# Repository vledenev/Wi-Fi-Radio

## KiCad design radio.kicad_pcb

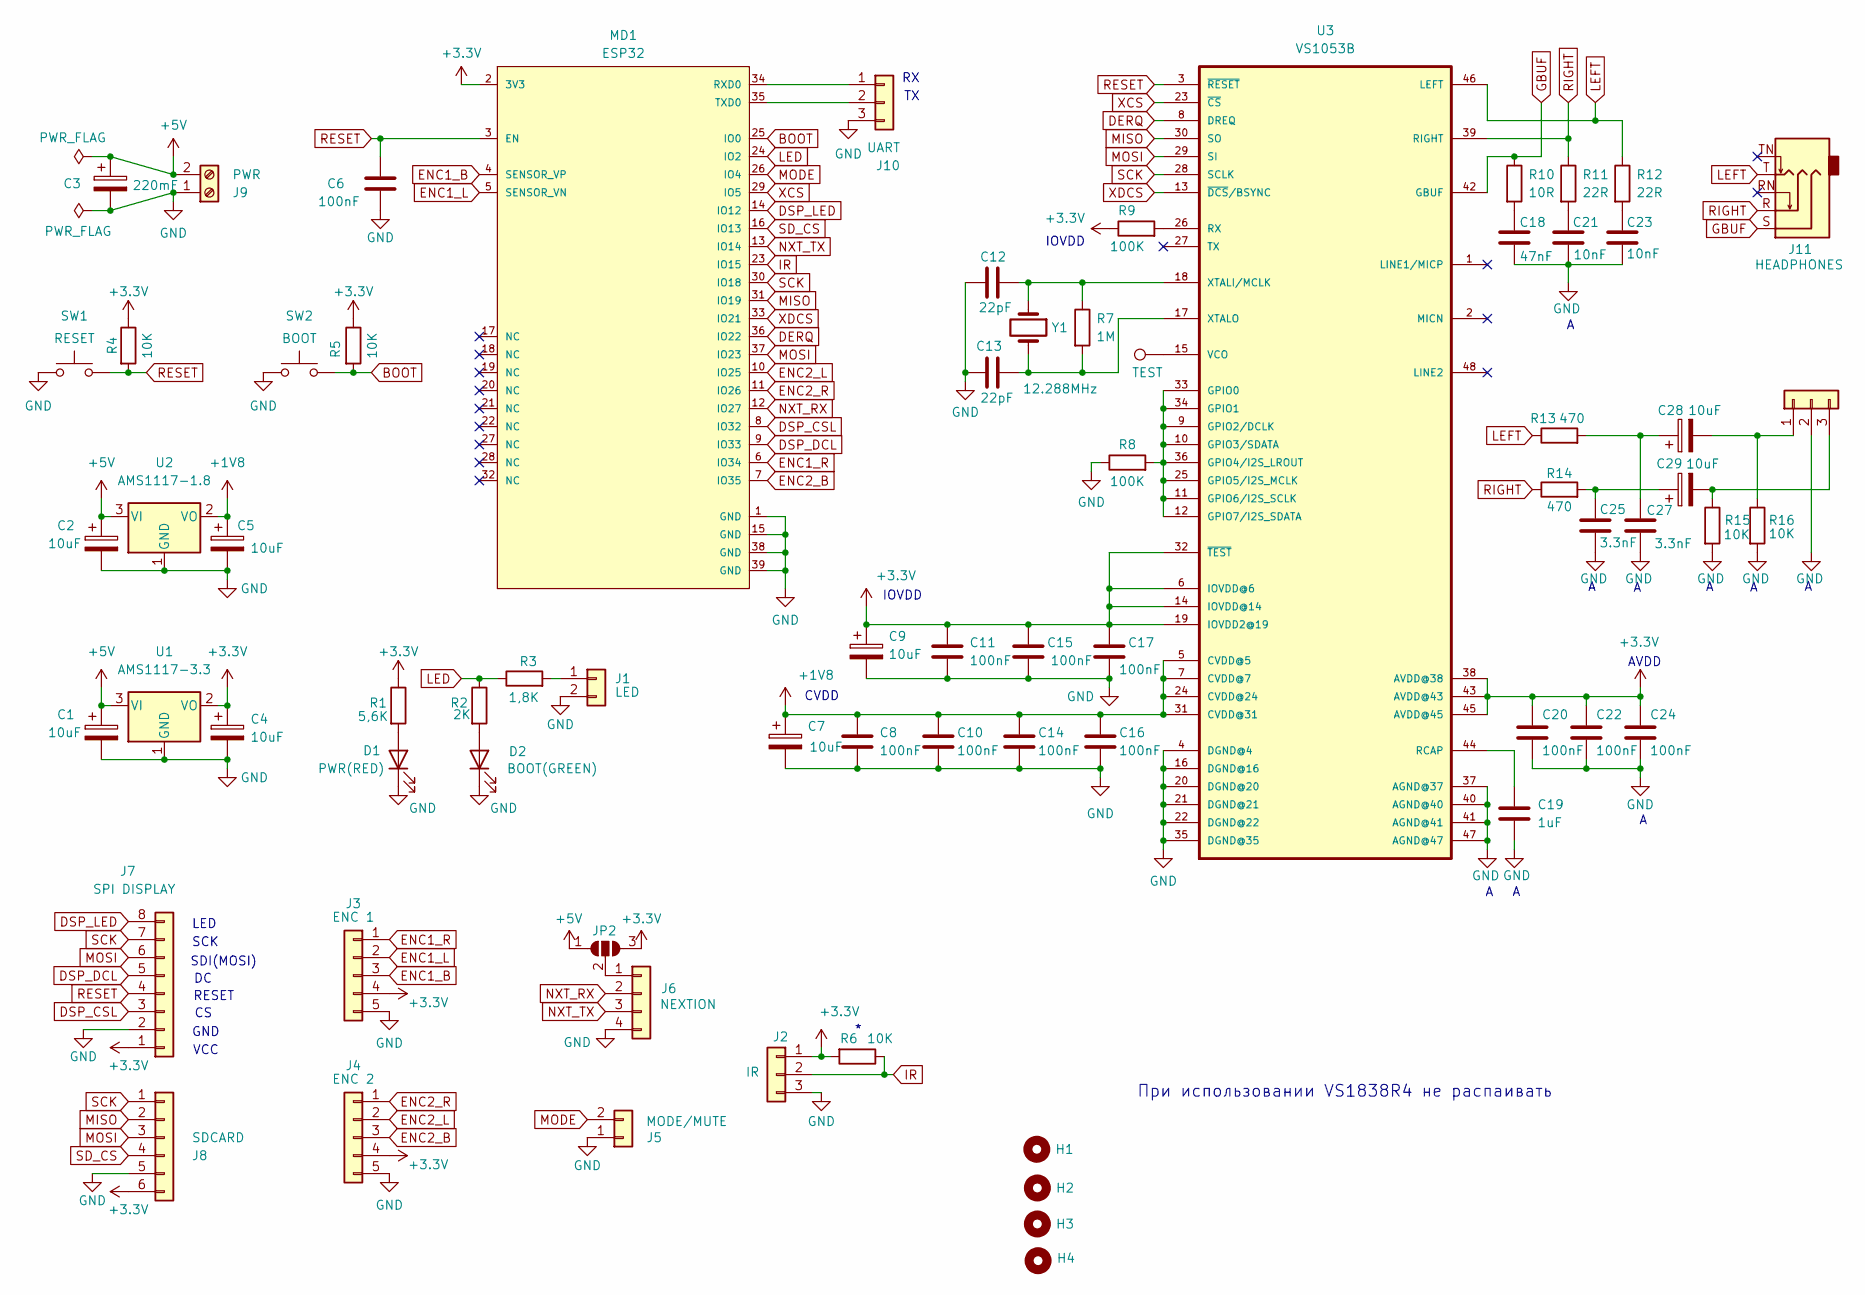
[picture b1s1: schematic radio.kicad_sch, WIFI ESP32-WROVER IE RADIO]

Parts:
C1, C2, C4, C5: 10uF; CP_EIA-3216-10_Kemet-I; LCSC C7171
C3: 220mF; CP_Elec_8x6.5; LCSC C249498
C6, C8, C10, C11, C14, C15, C16, C17, C20, C22, C24: 100nF; C_0805_2012Metric; LCSC C49678
C7, C9, C28, C29: 10uF; CP_EIA-3216-10_Kemet-I
C12, C13: 22pF; C_0805_2012Metric; LCSC C1804
C18: 47nF; C_0805_2012Metric; LCSC C53134
C19: 1uF; C_0805_2012Metric; LCSC C28323
C21, C23: 10nF; C_0805_2012Metric; LCSC C1710
C25, C27: 3.3nF; C_0805_2012Metric; LCSC C1738
D1: PWR(RED); LED_0805_2012Metric; LCSC C84256
D2: BOOT(GREEN); LED_0805_2012Metric; LCSC C84260
H1: MountingHole; MountingHole_2.7mm_M2.5
H2, H3, H4: MountingHole; MountingHole_2.7mm_M2.5_Pad_Via
J1: LED; JST_XH_B2B-XH-A_1x02_P2.50mm_Vertical
J2: IR; JST_XH_B3B-XH-A_1x03_P2.50mm_Vertical
J3: ENC 1; JST_XH_B5B-XH-A_1x05_P2.50mm_Vertical
J4: ENC 2; JST_XH_B5B-XH-A_1x05_P2.50mm_Vertical
J5: MODE/MUTE; JST_XH_B2B-XH-A_1x02_P2.50mm_Vertical
J6: NEXTION; JST_XH_B4B-XH-A_1x04_P2.50mm_Vertical
J7: SPI DISPLAY; JST_XH_B8B-XH-A_1x08_P2.50mm_Vertical
J8: SDCARD; JST_XH_B6B-XH-A_1x06_P2.50mm_Vertical
J9: PWR; TerminalBlock_4Ucon_1x02_P3.50mm_Horizontal
J10: UART; PinHeader_1x03_P2.54mm_Horizontal
J11: HEADPHONES; Jack_3.5mm_CUI_SJ1-3525N_Horizontal
J12: J12; JST_XH_B3B-XH-A_1x03_P2.50mm_Vertical
JP2: SolderJumper-3_P1.3mm_Open_RoundedPad1.0x1.5mm
MD1: ESP32; ESP32-WROVER-IE; digikey description RX TXRX MOD WIFI EXT IPEX SMD
R1: 5,6K; R_0805_2012Metric; LCSC C17398
R2: 2K; R_0805_2012Metric; LCSC C17513
R3: 1,8K; R_0805_2012Metric; LCSC C17398
R4, R5, R6, R15, R16: 10K; R_0805_2012Metric; LCSC C17414
R7: 1M; R_0805_2012Metric; LCSC C17514
R8, R9: 100K; R_0805_2012Metric; LCSC C149504
R10: 10R; R_0805_2012Metric; LCSC C17415
R11, R12: 22R; R_0805_2012Metric; LCSC C17544
R13, R14: 470; R_0805_2012Metric; LCSC C17710
SW1: RESET; SW_PUSH_6mm
SW2: BOOT; SW_PUSH_6mm
TP1: TEST; TestPoint_Pad_1.0x1.0mm
U1: AMS1117-3.3; SOT-223-3_TabPin2; LCSC C6186
U2: AMS1117-1.8; SOT-223-3_TabPin2; LCSC C6185
U3: VS1053B; LQFP-48_7x7mm_P0.5mm; LCSC C9922
Y1: 12.288MHz; Crystal_SMD_HC49-SD; LCSC C11240

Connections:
+1V8: C5.1, C7.1, C8.1, C10.1, C14.1, C16.1, U2.2 (VO), U3.5 (CVDD@5), U3.7 (CVDD@7), U3.24 (CVDD@24), U3.31 (CVDD@31)
+3.3V: C4.1, C9.1, C11.1, C15.1, C17.1, C20.1, C22.1, C24.1, J2.1, J3.4, J4.4, J7.1, J8.6, JP2.3 (B), MD1.2 (3V3), R1.1, R4.1, R5.1, R6.2, R9.1, U1.2 (VO), U3.6 (IOVDD@6), U3.14 (IOVDD@14), U3.19 (IOVDD2@19), U3.32 (~TEST), U3.38 (AVDD@38), U3.43 (AVDD@43), U3.45 (AVDD@45)
+5V: C1.1, C2.1, C3.1, J9.2, JP2.1 (A), U1.3 (VI), U2.3 (VI)
BOOT: MD1.25 (IO0), R5.2, SW2.2
DERQ: MD1.36 (IO22), U3.8 (DREQ)
DSP_CSL: J7.3, MD1.8 (IO32)
DSP_DCL: J7.5, MD1.9 (IO33)
DSP_LED: J7.8, MD1.14 (IO12)
ENC1_B: J3.3, MD1.4 (SENSOR_VP)
ENC1_L: J3.2, MD1.5 (SENSOR_VN)
ENC1_R: J3.1, MD1.6 (IO34)
ENC2_B: J4.3, MD1.7 (IO35)
ENC2_L: J4.2, MD1.10 (IO25)
ENC2_R: J4.1, MD1.11 (IO26)
GBUF: J11.S, R10.1, U3.42 (GBUF)
GND: C1.2, C2.2, C3.2, C4.2, C5.2, C6.2, C7.2, C8.2, C9.2, C10.2, C11.2, C12.2, C13.2, C14.2, C15.2, C16.2, C17.2, C18.2, C19.2, C20.2, C21.2, C22.2, C23.2, C24.2, C25.1, C27.1, D1.1 (K), D2.1 (K), J1.2, J2.3, J3.5, J4.5, J5.1, J6.4, J7.2, J8.5, J9.1, J10.3, J12.2, MD1.1 (GND), MD1.15 (GND), MD1.38 (GND), MD1.39 (GND), R8.1, R15.2, R16.2, SW1.1, SW2.1, U1.1 (GND), U2.1 (GND), U3.4 (DGND@4), U3.16 (DGND@16), U3.20 (DGND@20), U3.21 (DGND@21), U3.22 (DGND@22), U3.35 (DGND@35), U3.37 (AGND@37), U3.40 (AGND@40), U3.41 (AGND@41), U3.47 (AGND@47)
IR: J2.2, MD1.23 (IO15), R6.1
LED: MD1.24 (IO2), R2.1, R3.1
LEFT: J11.T, R12.1, R13.1, U3.46 (LEFT)
MISO: J8.2, MD1.31 (IO19), U3.30 (SO)
MODE: J5.2, MD1.26 (IO4)
MOSI: J7.6, J8.3, MD1.37 (IO23), U3.29 (SI)
NXT_RX: J6.2, MD1.12 (IO27)
NXT_TX: J6.3, MD1.13 (IO14)
unnamed: C18.1, R10.2
unnamed: C21.1, R11.2
unnamed: C23.1, R12.2
unnamed: C25.2, C29.1, R14.2
unnamed: C27.2, C28.1, R13.2
unnamed: D1.2 (A), R1.2
unnamed: D2.2 (A), R2.2
unnamed: J1.1, R3.2
unnamed: J6.1, JP2.2 (C)
unnamed: J10.1, MD1.34 (RXD0)
unnamed: J10.2, MD1.35 (TXD0)
unnamed: C28.2, J12.1, R16.1
unnamed: C29.2, J12.3, R15.1
unnamed: R8.2, U3.9 (GPIO2/DCLK), U3.10 (GPIO3/SDATA), U3.11 (GPIO6/I2S_SCLK), U3.12 (GPIO7/I2S_SDATA), U3.25 (GPIO5/I2S_MCLK), U3.33 (GPIO0), U3.34 (GPIO1), U3.36 (GPIO4/I2S_LROUT)
unnamed: C19.1, U3.44 (RCAP)
unnamed: R9.2, U3.26 (RX)
unnamed: TP1.1, U3.15 (VCO)
unnamed: C12.1, R7.1, U3.18 (XTALI/MCLK), Y1.1
unnamed: C13.1, R7.2, U3.17 (XTALO), Y1.2
RESET: C6.1, J7.4, MD1.3 (EN), R4.2, SW1.2, U3.3 (~RESET)
RIGHT: J11.R, R11.1, R14.1, U3.39 (RIGHT)
SCK: J7.7, J8.1, MD1.30 (IO18), U3.28 (SCLK)
SD_CS: J8.4, MD1.16 (IO13)
XCS: MD1.29 (IO5), U3.23 (~CS)
XDCS: MD1.33 (IO21), U3.13 (~DCS/BSYNC)

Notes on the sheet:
При использовании VS1838R4 не распаивать
GND
AVDD
SDI(MOSI)
RESET
LED
SCK
IOVDD
CVDD
VCC

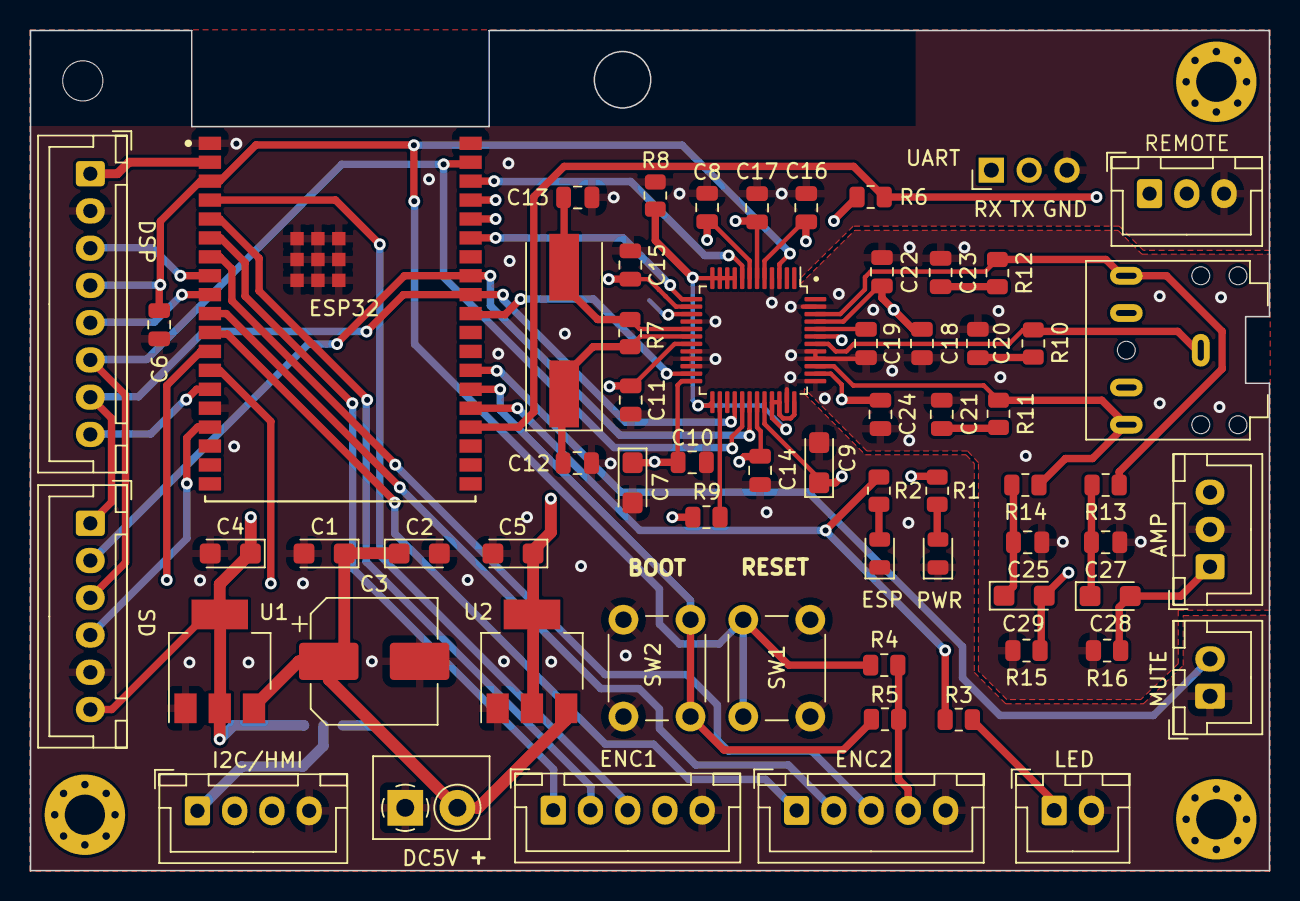
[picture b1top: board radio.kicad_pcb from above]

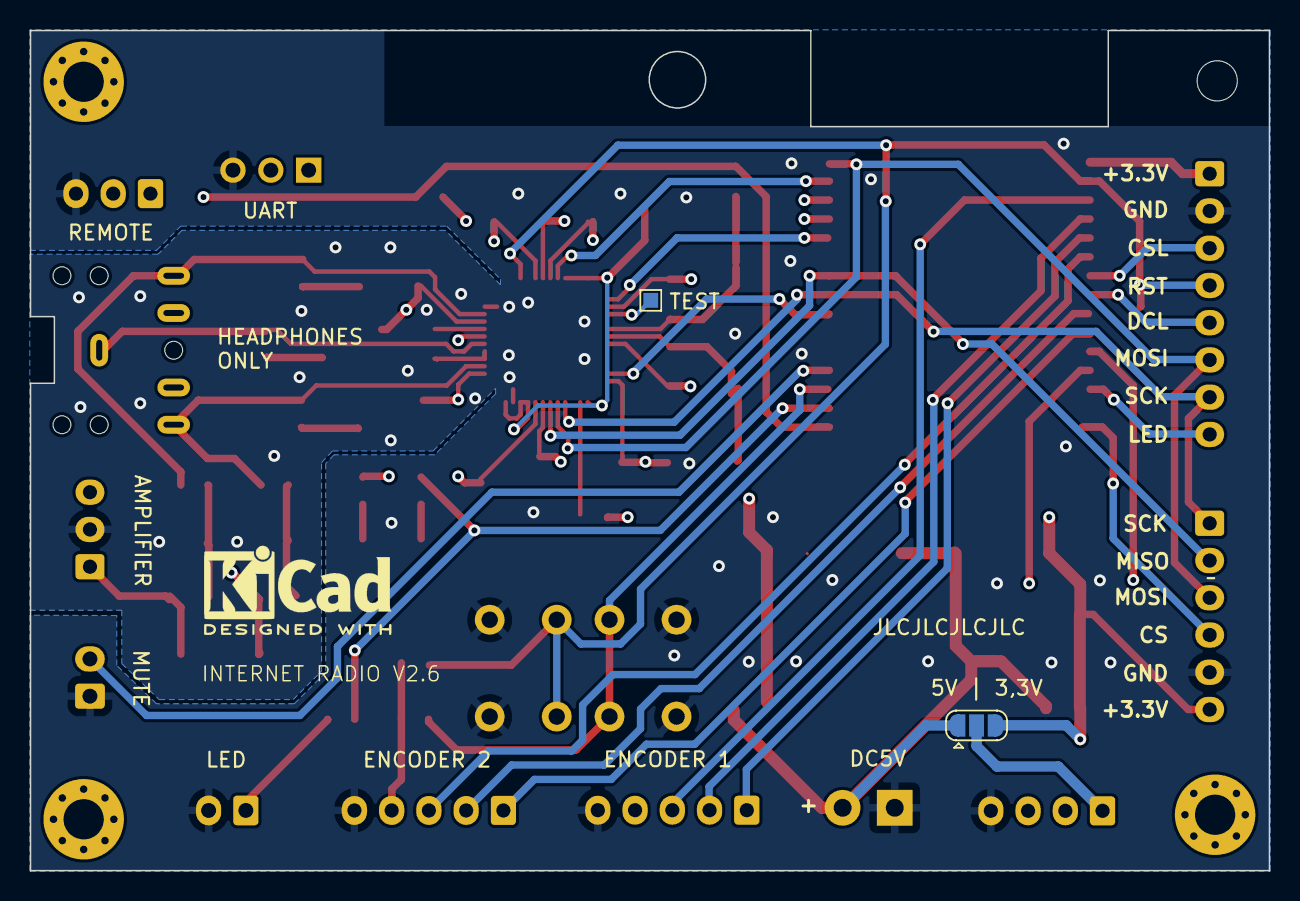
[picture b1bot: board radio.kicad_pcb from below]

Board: 4 copper layers, 83.2 x 56.4 mm, 71 parts (2 on the bottom side), 49 nets.

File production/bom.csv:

Designator,Footprint,Quantity,Value,LCSC Part #
"C1, C2, C28, C29, C4, C5, C7, C9",CP_EIA-3216-10_Kemet-I,8,10uF,C7171
C10,0805,1,100nF,C49678
C11,0805,1,100nF,C49678
C12,0805,1,22pF,C1804
C13,0805,1,22pF,C1804
C14,0805,1,100nF,C49678
C15,0805,1,100nF,C49678
C16,0805,1,100nF,C49678
C17,0805,1,100nF,C49678
C18,0805,1,47nF,C53134
C19,0805,1,1uF,C28323
C20,0805,1,100nF,C49678
C21,0805,1,10nF,C1710
C22,0805,1,100nF,C49678
C23,0805,1,10nF,C1710
C24,0805,1,100nF,C49678
C25,0805,1,3.3nF,C1738
C27,0805,1,3.3nF,C1738
C3,CP_Elec_8x6.5,1,220mF,C249498
C6,0805,1,100nF,C49678
C8,0805,1,100nF,C49678
D1,0805,1,PWR(RED),C84256
D2,0805,1,BOOT(GREEN),C84260
MD1,ESP32-WROVER-IE,1,ESP32,C701350
R1,0805,1,"1,8K",C17398
R10,0805,1,10R,C17415
R11,0805,1,20R,C17544
R12,0805,1,20R,C17544
R13,0805,1,470,C17710
R14,0805,1,470,C17710
R15,0805,1,10K,C17414
R16,0805,1,10K,C17414
R2,0805,1,1K,C17513
R3,0805,1,"1,8K",C17398
R4,0805,1,10K,C17414
R5,0805,1,10K,C17414
R6,0805,1,10K,C17414
R7,0805,1,1M,C17514
R8,0805,1,100K,C149504
R9,0805,1,100K,C149504
U1,SOT-223-3_TabPin2,1,AMS1117-3.3,C6186
U2,SOT-223-3_TabPin2,1,AMS1117-1.8,C6185
U3,LQFP-48_7x7mm_P0.5mm,1,VS1053B,C9922
Y1,Crystal_SMD_HC49-SD,1,12.288MHz,C11240
